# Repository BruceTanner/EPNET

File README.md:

# EPNET
Enterprise Computer Network Interface

This project is hardware and software for a network interface card for the Enterprise computer.

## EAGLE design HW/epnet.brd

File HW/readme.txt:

These files are the schematic and PCB layout for EPNET.

==============================================================================

 Copyright (C) 2015  Bruce Tanner

    These files are free: you can redistribute them and/or modify
    them under the terms of the GNU General Public License as published by
    the Free Software Foundation, either version 3 of the License, or
    (at your option) any later version.

    These files are distributed in the hope that they will be useful,
    but WITHOUT ANY WARRANTY; without even the implied warranty of
    MERCHANTABILITY or FITNESS FOR A PARTICULAR PURPOSE.  See the
    GNU General Public License for more details.

    You should have received a copy of the GNU General Public License
    along with this program.  If not, see <http://www.gnu.org/licenses/>.

 If you do use or modify these files, either for their original purpose or for
 something new, I'd love to hear about it! I can be contacted by email at:

 brucetanner@btopenworld.com

==============================================================================

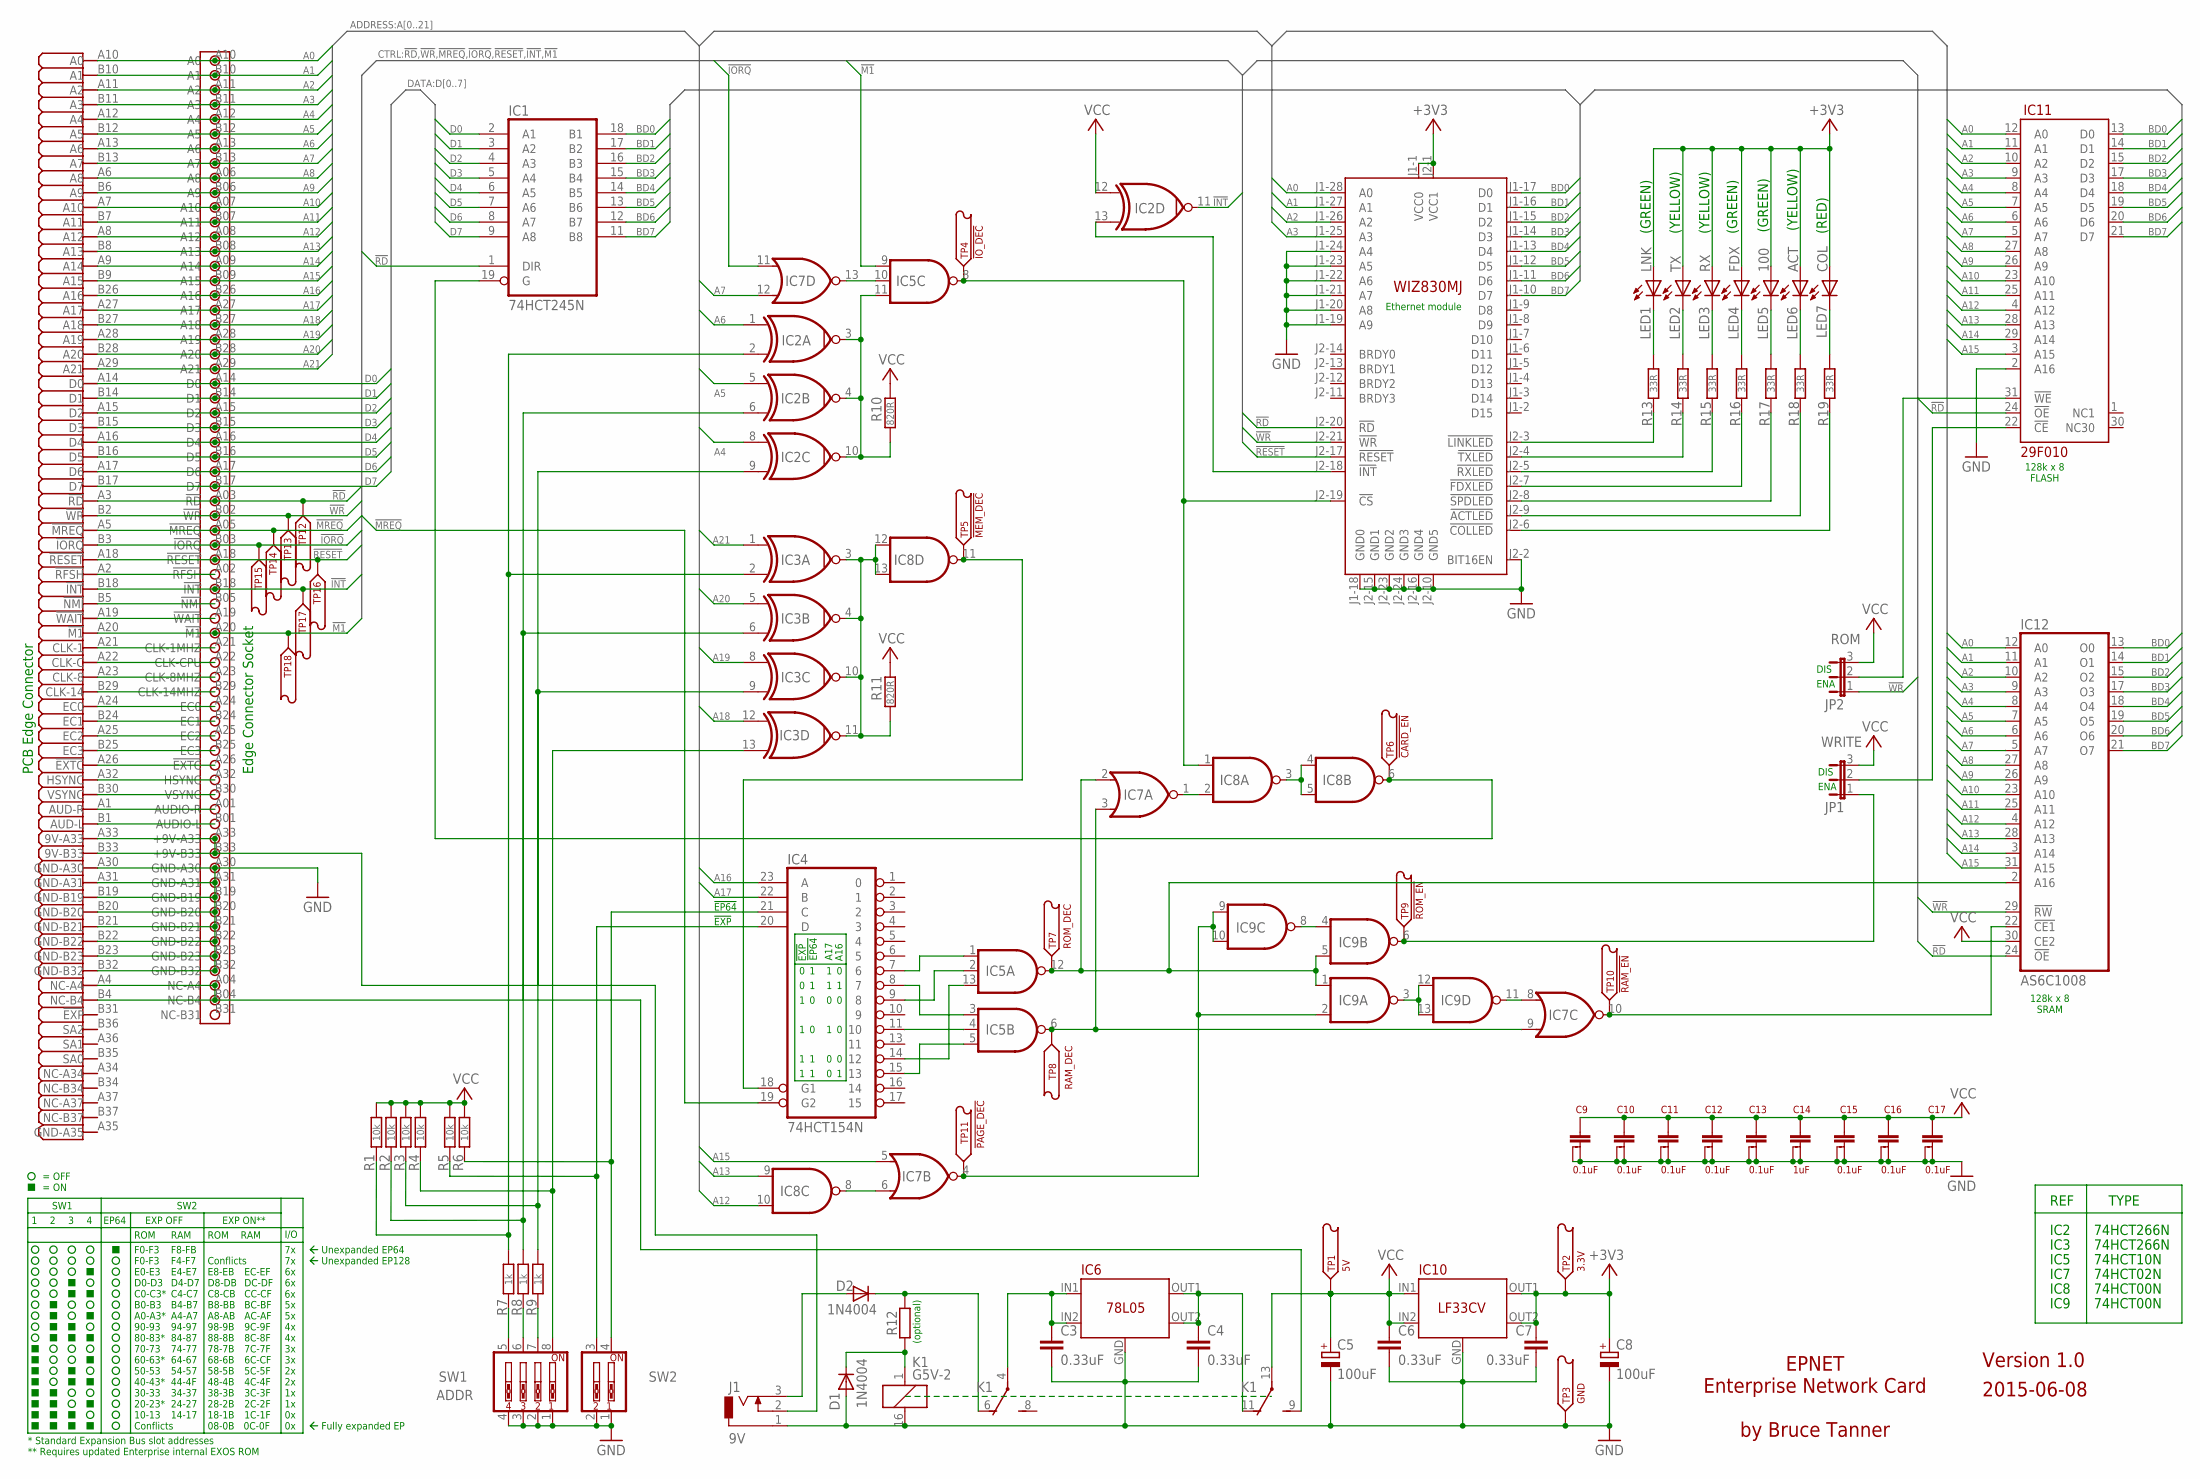
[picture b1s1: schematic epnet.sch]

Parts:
C1: Edge Connector; CON-EDGE
C2: CON-EXPANSION; EXPSOCKET
C3, C4, C6, C7: 0.33uF; C050-025X075
C5, C8: 100uF; E2,5-7
C9, C10, C11, C12, C13, C15, C16, C17: 0.1uF; CAPACITOR
C14: 1uF; CAPACITOR
D1, D2: 1N4004; DO41-10
IC1: 74HCT245N; DIL20
IC2, IC3: 74LS266N; DIL14
IC4: 74HCT154N; DIL24-6
IC5: 74AS10N; DIL14
IC6: 78L05; REGULATOR
IC7: 74LS02N; DIL14
IC8, IC9: 74LS00N; DIL14
IC10: LF33CV; REGULATOR
IC11: 29F010; 20F010
IC12: AS6C1008; DIL32
J1: 9V; DCJ0202
JP1: WRITE; JP2
JP2: ROM; JP2
K1: G5V-2
LED1: LNK; LED3MM
LED2: TX; LED3MM
LED3: RX; LED3MM
LED4: FDX; LED3MM
LED5: 100; LED3MM
LED6: ACT; LED3MM
LED7: COL; LED3MM
M1: WIZ830MJ
R1, R2, R3, R4, R5, R6: 10k; 0309/10
R7, R8, R9: 1k; 0309/10
R10, R11: 820R; 0309/10
R12: R-EU_0309/10; 0309/10
R13, R14, R15, R16, R17, R18, R19: 33R; 0309/10
SW1: ADDR; EDG-04
SW2: SW_DIP-2; EDG-02
TP1: 5V; TESTPOINT
TP2: 3.3V; TESTPOINT
TP3: GND; TESTPOINT
TP4: !IO_DEC; TESTPOINT
TP5: !MEM_DEC; TESTPOINT
TP6: !CARD_EN; TESTPOINT
TP7: ROM_DEC; TESTPOINT
TP8: RAM_DEC; TESTPOINT
TP9: !ROM_EN; TESTPOINT
TP10: !RAM_EN; TESTPOINT
TP11: !PAGE_DEC; TESTPOINT
TP12: !RD; TESTPOINT
TP13: !WR; TESTPOINT
TP14: !MREQ; TESTPOINT
TP15: !IORQ; TESTPOINT
TP16: !RESET; TESTPOINT
TP17: !INT; TESTPOINT
TP18: !M1; TESTPOINT

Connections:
!CARD_ENABLE: IC1.19 (G), IC8.6 (O), TP6.P$1
!EP64: IC4.21 (C), R6.1, SW2.4
!INT: C1.B18 (!INT), C2.B18 (!INT), IC2.11 (O), TP17.P$1
!IORQ: C1.B3 (!IORQ), C2.B03 (!IORQ), IC7.11 (I0), TP15.P$1
!IO_DECODE: IC5.8 (O), IC8.1 (I0), M1.J2-19 (!CS), TP4.P$1
!M1: C1.A20 (!M1), C2.A20 (!M1), IC5.9 (I0), TP18.P$1
!MEM_DEC: IC4.18 (G1), IC8.11 (O), TP5.P$1
!MREQ: C1.A5 (!MREQ), C2.A05 (!MREQ), IC4.19 (G2), TP14.P$1
!RAM_ENABLE: IC7.10 (O), IC12.22 (!CE1), TP10.P$1
!RD: C1.A3 (!RD), C2.A03 (!RD), IC1.1 (DIR), IC11.24 (!OE), IC12.24 (!OE), M1.J2-20 (!RD), TP12.P$1
!RESET: C1.A18 (!RESET), C2.A18 (!RESET), M1.J2-17 (!RESET), TP16.P$1
!ROM_ENABLE: IC9.6 (O), JP1.1, TP9.P$1
!WR: C1.B2 (!WR), C2.B02 (!WR), IC12.29 (!RW), JP2.1, M1.J2-21 (!WR), TP13.P$1
+3V3: C7.1, C8.+, IC10.OUT1, IC10.OUT2, LED1.A, LED2.A, LED3.A, LED4.A, LED5.A, LED6.A, LED7.A, M1.J1-1 (VCC0), M1.J2-1 (VCC1), TP2.P$1
A0: C1.A10 (A0), C2.A10 (A0), IC11.12 (A0), IC12.12 (A0), M1.J1-28 (A0)
A1: C1.B10 (A1), C2.B10 (A1), IC11.11 (A1), IC12.11 (A1), M1.J1-27 (A1)
A2: C1.A11 (A2), C2.A11 (A2), IC11.10 (A2), IC12.10 (A2), M1.J1-26 (A2)
A3: C1.B11 (A3), C2.B11 (A3), IC11.9 (A3), IC12.9 (A3), M1.J1-25 (A3)
A4: C1.A12 (A4), C2.A12 (A4), IC2.8 (I0), IC11.8 (A4), IC12.8 (A4)
A5: C1.B12 (A5), C2.B12 (A5), IC2.5 (I0), IC11.7 (A5), IC12.7 (A5)
A6: C1.A13 (A6), C2.A13 (A6), IC2.1 (I0), IC11.6 (A6), IC12.6 (A6)
A7: C1.B13 (A7), C2.B13 (A7), IC7.12 (I1), IC11.5 (A7), IC12.5 (A7)
A8: C1.A6 (A8), C2.A06 (A8), IC11.27 (A8), IC12.27 (A8)
A9: C1.B6 (A9), C2.B06 (A9), IC11.26 (A9), IC12.26 (A9)
A10: C1.A7 (A10), C2.A07 (A10), IC11.23 (A10), IC12.23 (A10)
A11: C1.B7 (A11), C2.B07 (A11), IC11.25 (A11), IC12.25 (A11)
A12: C1.A8 (A12), C2.A08 (A12), IC8.10 (I1), IC11.4 (A12), IC12.4 (A12)
A13: C1.B8 (A13), C2.B08 (A13), IC8.9 (I0), IC11.28 (A13), IC12.28 (A13)
A14: C1.A9 (A14), C2.A09 (A14), IC11.29 (A14), IC12.3 (A14)
A15: C1.B9 (A15), C2.B09 (A15), IC7.5 (I0), IC11.3 (A15), IC12.31 (A15)
A16: C1.B26 (A16), C2.B26 (A16), IC4.23 (A)
A17: C1.A27 (A17), C2.A27 (A17), IC4.22 (B)
A18: C1.B27 (A18), C2.B27 (A18), IC3.12 (I0)
A19: C1.A28 (A19), C2.A28 (A19), IC3.8 (I0)
A20: C1.B28 (A20), C2.B28 (A20), IC3.5 (I0)
A21: C1.A29 (A21), C2.A29 (A21), IC3.1 (I0)
BD0: IC1.18 (B1), IC11.13 (D0), IC12.13 (O0), M1.J1-17 (D0)
BD1: IC1.17 (B2), IC11.14 (D1), IC12.14 (O1), M1.J1-16 (D1)
BD2: IC1.16 (B3), IC11.15 (D2), IC12.15 (O2), M1.J1-15 (D2)
BD3: IC1.15 (B4), IC11.17 (D3), IC12.17 (O3), M1.J1-14 (D3)
BD4: IC1.14 (B5), IC11.18 (D4), IC12.18 (O4), M1.J1-13 (D4)
BD5: IC1.13 (B6), IC11.19 (D5), IC12.19 (O5), M1.J1-12 (D5)
BD6: IC1.12 (B7), IC11.20 (D6), IC12.20 (O6), M1.J1-11 (D6)
BD7: IC1.11 (B8), IC11.21 (D7), IC12.21 (O7), M1.J1-10 (D7)
D0: C1.A14 (D0), C2.A14 (D0), IC1.2 (A1)
D1: C1.B14 (D1), C2.B14 (D1), IC1.3 (A2)
D2: C1.A15 (D2), C2.A15 (D2), IC1.4 (A3)
D3: C1.B15 (D3), C2.B15 (D3), IC1.5 (A4)
D4: C1.A16 (D4), C2.A16 (D4), IC1.6 (A5)
D5: C1.B16 (D5), C2.B16 (D5), IC1.7 (A6)
D6: C1.A17 (D6), C2.A17 (D6), IC1.8 (A7)
D7: C1.B17 (D7), C2.B17 (D7), IC1.9 (A8)
GND: C1.A30 (GND-A30), C1.A31 (GND-A31), C1.B19 (GND-B19), C1.B20 (GND-B20), C1.B21 (GND-B21), C1.B22 (GND-B22), C1.B23 (GND-B23), C1.B32 (GND-B32), C2.A30 (GND-A30), C2.A31 (GND-A31), C2.B19 (GND-B19), C2.B20 (GND-B20), C2.B21 (GND-B21), C2.B22 (GND-B22), C2.B23 (GND-B23), C2.B32 (GND-B32), C3.2, C4.2, C5.-, C6.2, C7.2, C8.-, C9.P$2, C9.P$3, C10.P$2, C10.P$3, C11.P$2, C11.P$3, C12.P$2, C12.P$3, C13.P$2, C13.P$3, C14.P$2, C14.P$3, C15.P$2, C15.P$3, C16.P$2, C16.P$3, C17.P$2, C17.P$3, D1.A, IC1.10 (GND), IC2.7 (GND), IC3.7 (GND), IC4.12 (GND), IC5.7 (GND), IC6.GND, IC7.7 (GND), IC8.7 (GND), IC9.7 (GND), IC10.GND, IC11.2 (A16), IC11.16 (GND), IC12.16 (GND), J1.1, K1.16 (2), M1.J1-18 (GND0), M1.J1-19 (A9), M1.J1-20 (A8), M1.J1-21 (A7), M1.J1-22 (A6), M1.J1-23 (A5), M1.J1-24 (A4), M1.J2-2 (BIT16EN), M1.J2-10 (GND5), M1.J2-15 (GND1), M1.J2-16 (GND4), M1.J2-23 (GND2), M1.J2-24 (GND3), SW1.1, SW1.2, SW1.3, SW1.4, SW2.1, SW2.2, TP3.P$1
GND-A35: C1.A35 (GND-A35)
unnamed: C1.A2 (!RFSH), C2.A02 (!RFSH)
unnamed: IC9.4 (I0), IC9.8 (O)
unnamed: R7.1, SW1.5
unnamed: IC3.13 (I1), R4.1, SW1.8
unnamed: R8.1, SW1.6
unnamed: R9.1, SW1.7
unnamed: M1.J2-3 (!LINKLED), R13.1
unnamed: IC4.7 (6), IC5.1 (I0)
unnamed: IC5.10 (I1), IC7.13 (O)
unnamed: IC4.8 (7), IC5.3 (I0)
unnamed: IC4.15 (13), IC5.5 (I2)
unnamed: IC2.9 (I1), IC3.9 (I1), R3.1, R9.2
unnamed: M1.J2-4 (!TXLED), R14.1
unnamed: IC9.3 (O), IC9.12 (I0), IC9.13 (I1)
unnamed: IC4.9 (8), IC5.2 (I1)
unnamed: IC4.11 (10), IC5.4 (I1)
unnamed: IC4.14 (12), IC5.13 (I2)
unnamed: IC7.1 (O), IC8.2 (I1)
unnamed: IC7.8 (I0), IC9.11 (O)
unnamed: C1.B5 (!NMI), C2.B05 (!NMI)
unnamed: D1.C, K1.1, R12.1
unnamed: IC8.3 (O), IC8.4 (I0), IC8.5 (I1)
unnamed: IC7.6 (I1), IC8.8 (O)
unnamed: M1.J2-5 (!RXLED), R15.1
unnamed: M1.J2-7 (!FDXLED), R16.1
unnamed: M1.J2-8 (!SPDLED), R17.1
unnamed: M1.J2-9 (!ACTLED), R18.1
unnamed: M1.J2-6 (!COLLED), R19.1
unnamed: LED1.K (C), R13.2
unnamed: LED2.K (C), R14.2
unnamed: LED3.K (C), R15.2
unnamed: LED4.K (C), R16.2
unnamed: LED5.K (C), R17.2
unnamed: LED6.K (C), R18.2
unnamed: LED7.K (C), R19.2
unnamed: IC2.3 (O), IC2.4 (O), IC2.10 (O), IC5.11 (I2), R10.1
unnamed: IC3.3 (O), IC3.4 (O), IC3.10 (O), IC3.11 (O), IC8.12 (I0), IC8.13 (I1), R11.1
unnamed: IC4.20 (D), R5.1, SW2.3
unnamed: D2.C, K1.6 (O), R12.2
unnamed: D2.A, J1.3
unnamed: C1.A33 (9V-A33), C1.B33 (9V-B33), C2.A33 (+9V-A33), C2.B33 (+9V-B33), J1.2
unnamed: IC11.22 (!CE), JP1.2
unnamed: IC11.31 (!WE), JP2.2
unnamed: C1.A19 (!WAIT), C2.A19 (!WAIT)
unnamed: C1.A21 (CLK-1), C2.A21 (CLK-1MHZ)
unnamed: C1.A22 (CLK-C), C2.A22 (CLK-CPU)
unnamed: C1.A23 (CLK-8), C2.A23 (CLK-8MHZ)
unnamed: C1.B29 (CLK-14), C2.B29 (CLK-14MHZ)
unnamed: C1.A24 (EC0), C2.A24 (EC0)
unnamed: C1.B24 (EC1), C2.B24 (EC1)
unnamed: C1.A25 (EC2), C2.A25 (EC2)
unnamed: C1.B25 (EC3), C2.B25 (EC3)
unnamed: C1.A26 (!EXTC), C2.A26 (!EXTC)
unnamed: C1.A32 (HSYNC), C2.A32 (HSYNC)
unnamed: C1.B30 (VSYNC), C2.B30 (VSYNC)
unnamed: C1.A1 (AUD-R), C2.A01 (AUDIO-R)
unnamed: C1.B1 (AUD-L), C2.B01 (AUDIO-L)
unnamed: C3.1, IC6.IN1, IC6.IN2, K1.4
unnamed: C1.A4 (NC-A4), C1.B4 (NC-B4), C2.A04 (NC-A4), C2.B04 (NC-B4), K1.9 (S)
unnamed: C4.1, IC6.OUT1, IC6.OUT2, K1.11 (O)
unnamed: IC2.13 (I1), M1.J2-18 (!INT)
PAGE_DECODE: IC7.4 (O), IC9.2 (I1), IC9.9 (I0), IC9.10 (I1), TP11.P$1
RAM_DECODE: IC5.6 (O), IC7.3 (I1), IC7.9 (I1), TP8.P$1
ROM_DECODE: IC5.12 (O), IC7.2 (I0), IC9.1 (I0), IC9.5 (I1), IC12.2 (A16), TP7.P$1
SA1: IC2.6 (I1), IC3.6 (I1), R2.1, R8.2
SA2: IC2.2 (I1), IC3.2 (I1), R1.1, R7.2
VCC: C5.+, C6.1, C9.P$1, C10.P$1, C11.P$1, C12.P$1, C13.P$1, C14.P$1, C15.P$1, C16.P$1, C17.P$1, IC1.20 (VCC), IC2.12 (I0), IC2.14 (VCC), IC3.14 (VCC), IC4.24 (VCC), IC5.14 (VCC), IC7.14 (VCC), IC8.14 (VCC), IC9.14 (VCC), IC10.IN1, IC10.IN2, IC11.32 (VCC), IC12.30 (CE2), IC12.32 (VCC), JP1.3, JP2.3, K1.13, R1.2, R2.2, R3.2, R4.2, R5.2, R6.2, R10.2, R11.2, TP1.P$1

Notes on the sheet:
74HCT266N
!EP64
!EXP
EPNET Enterprise Network Card by Bruce Tanner
2015-06-08
74HCT10N
74HCT00N
74HCT02N
REF
TYPE
IC2
IC3
IC7
IC5
IC9
IC8
ROM
RAM
I/O
F0-F3
F4-F7
F8-FB
D0-D3
D4-D7
E0-E3
E4-E7
C0-C3*
C4-C7
B0-B3
B4-B7
A8-AB
AC-AF
90-93
94-97
88-8B
8C-8F
68-6B
6C-CF
70-73
74-77

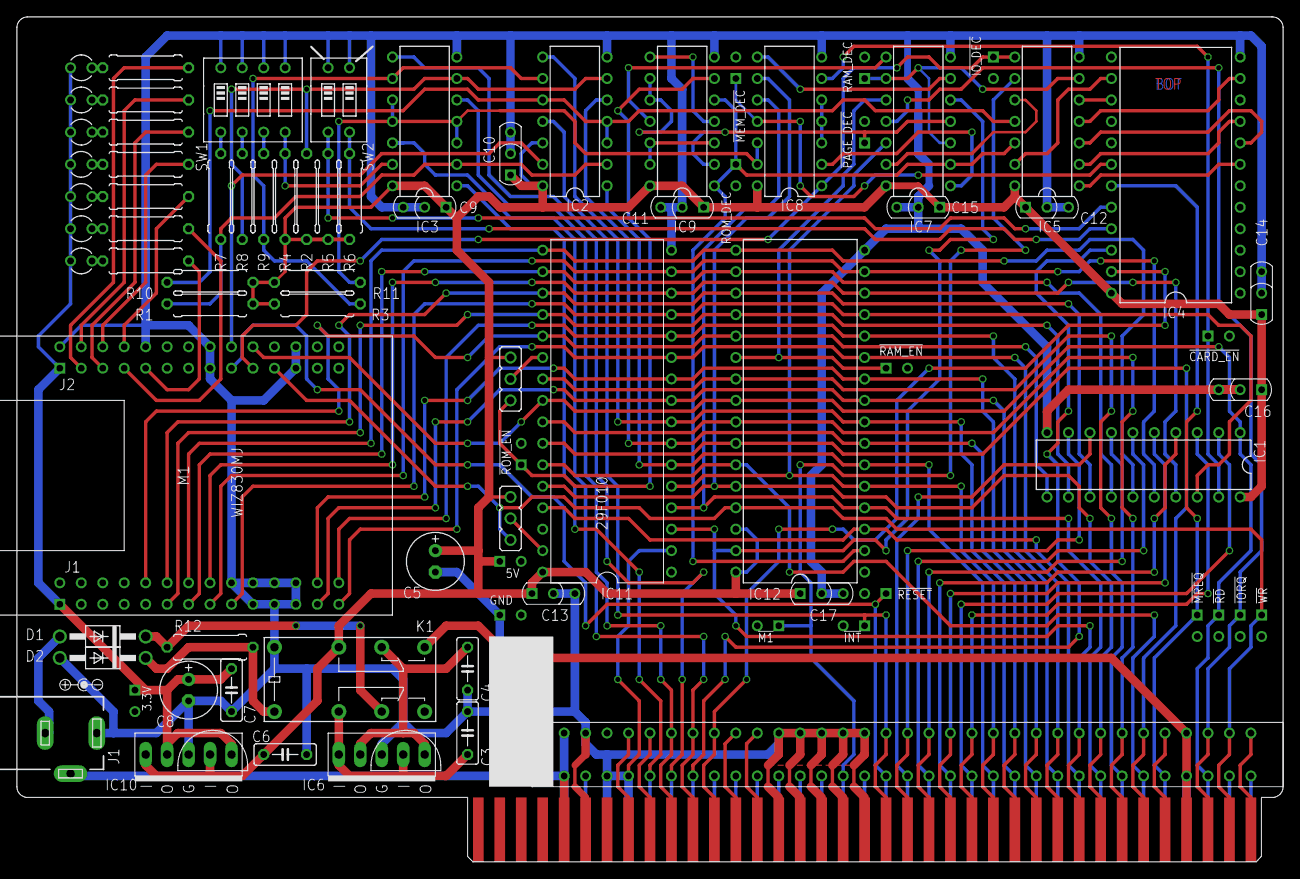
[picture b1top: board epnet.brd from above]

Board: 2 copper layers, 149.9 x 100.0 mm, 82 parts (0 on the bottom side), 120 nets.

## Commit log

2015-11-03 :space_invader: Added .gitattributes & .gitignore files
2015-11-03 Initial version on Github
2015-11-17 No RAM sub-page
2015-12-06 Initial Version of Manual on GitHub
